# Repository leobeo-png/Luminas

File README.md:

# Luminas
Rhythm game controller development (Pro Micro). WIP <br>
[Video Demo](https://www.youtube.com/watch?v=vNHZUSEBsMY "Early Prototype")
[Video Demo](https://www.youtube.com/watch?v=JDYHQ-9xTno "Prototype Update")
---
## Description
 - Custom keyboard NKRO HID 
 - PCB size for 15.6" laptop
 - ToF sensors instead of IR for compactness
---
## Components Used:
 - Arduino Pro Micro
 - MPR121 Modules x3
 - VL53L0X ToF sensors x2 
 - TCA9548 I2C Multiplexer
 - Pull-up resistors
---
## Goals
 - Improve the design of the PCB 
 - Reaserch and design the casing
--- 
## What I Learnt so Far 
 - HID (descriptors, how NKRO works)
 - PCB schematic designing
 - Diving further into I2C

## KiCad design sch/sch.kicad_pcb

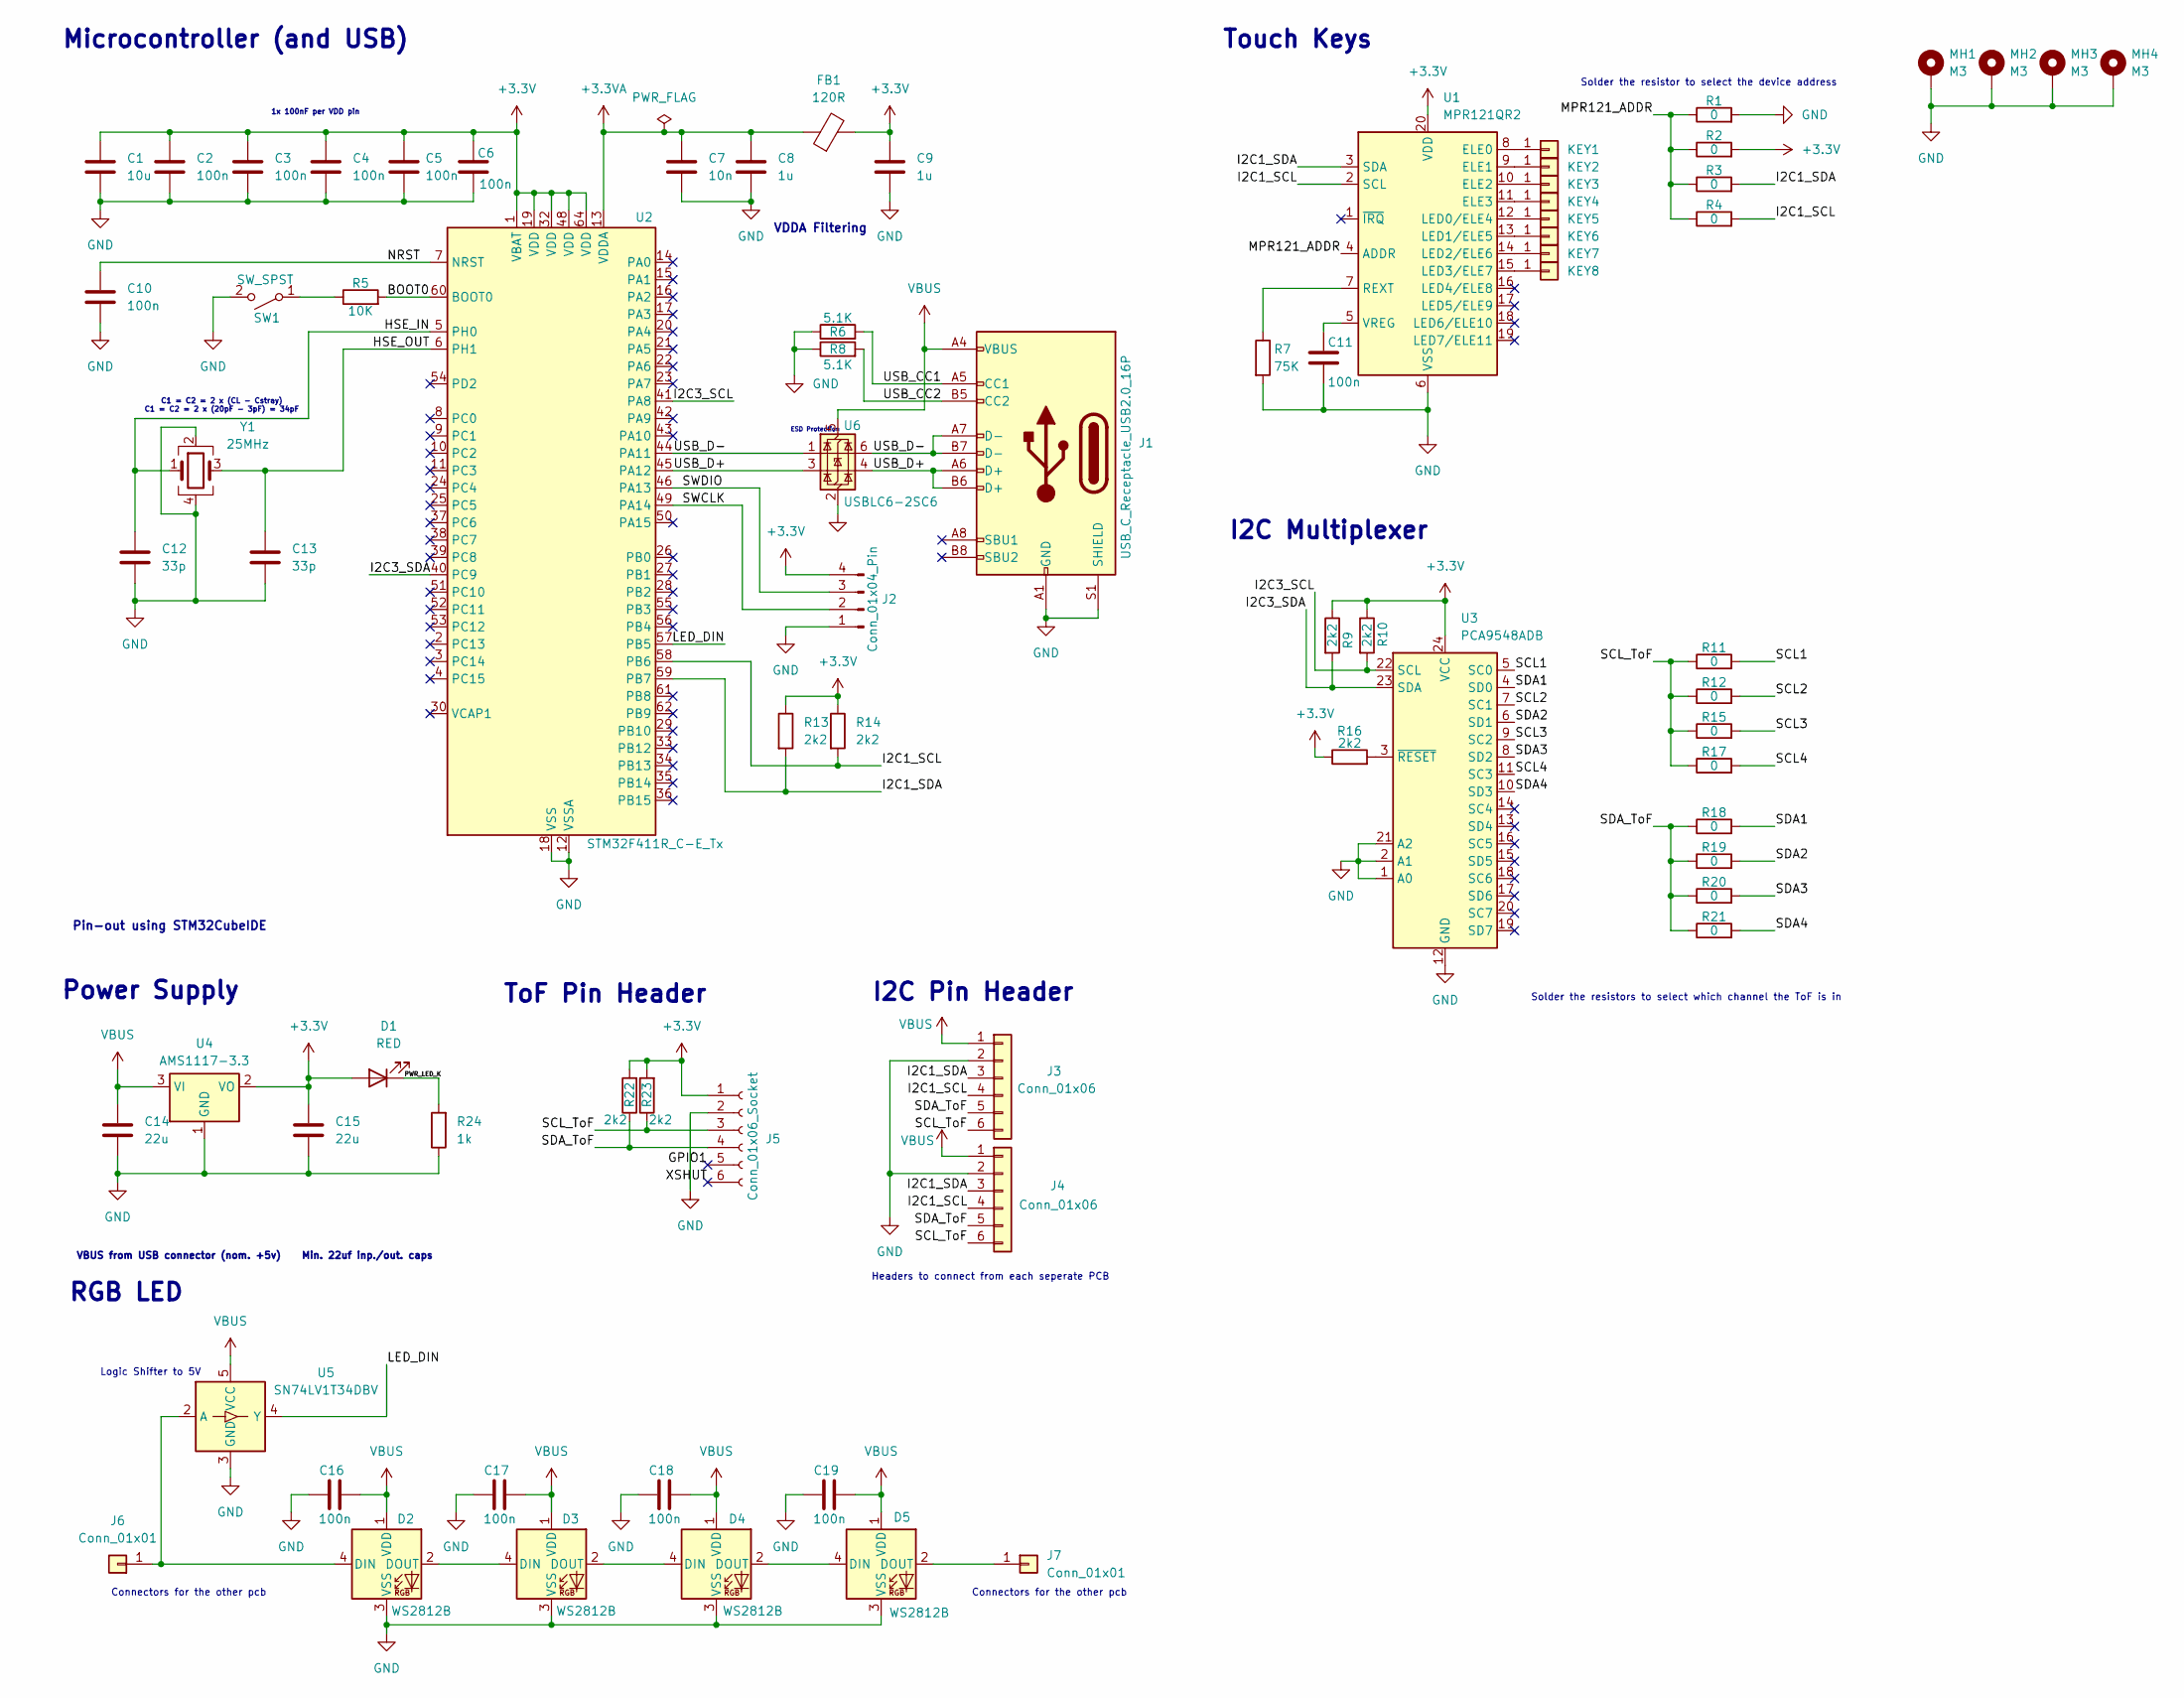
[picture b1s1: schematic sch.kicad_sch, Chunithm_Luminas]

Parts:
C1: 10u; C_0603_1608Metric_Pad1.08x0.95mm_HandSolder
C2, C3, C4, C5, C6, C10, C11, C16, C17, C18, C19: 100n; C_0603_1608Metric_Pad1.08x0.95mm_HandSolder
C7: 10n; C_0603_1608Metric_Pad1.08x0.95mm_HandSolder
C8, C9: 1u; C_0603_1608Metric_Pad1.08x0.95mm_HandSolder
C12, C13: 33p; C_0603_1608Metric_Pad1.08x0.95mm_HandSolder
C14, C15: 22u; C_0805_2012Metric
D1: RED; LED_0201_0603Metric
D2, D3, D4, D5: WS2812B; LED_WS2812B_PLCC4_5.0x5.0mm_P3.2mm
FB1: 120R; L_0603_1608Metric
J1: USB_C_Receptacle_USB2.0_16P; USB_C_Receptacle_GCT_USB4105-xx-A_16P_TopMnt_Horizontal
J2: Conn_01x04_Pin; PinHeader_1x04_P2.54mm_Vertical
J3, J4: Conn_01x06; Conn_Solder_I2C
J5: Conn_01x06_Socket; PinHeader_1x06_P2.54mm_Vertical
J6, J7: Conn_01x01; Solder_3P
KEY1, KEY2, KEY3, KEY4, KEY5, KEY6, KEY7, KEY8: Conn_01x01; ChuKey
MH1, MH2, MH3, MH4: M3; MountingHole_3.2mm_M3_Pad_Via
R1, R2, R3, R4, R11, R12, R15, R17, R18, R19, R20, R21: 0; R_0603_1608Metric_Pad0.98x0.95mm_HandSolder
R5: 10K; R_0603_1608Metric_Pad0.98x0.95mm_HandSolder
R6, R8: 5.1K; R_0603_1608Metric_Pad0.98x0.95mm_HandSolder
R7: 75K; R_0603_1608Metric_Pad0.98x0.95mm_HandSolder
R9, R10, R13, R14, R16, R22, R23: 2k2; R_0603_1608Metric_Pad0.98x0.95mm_HandSolder
R24: 1k; R_0603_1608Metric_Pad0.98x0.95mm_HandSolder
SW1: SW_SPST; SW_SPST_TS-1088-xR025
U1: MPR121QR2; UQFN-20_3x3mm_P0.4mm
U2: STM32F411R_C-E_Tx; LQFP-64_10x10mm_P0.5mm
U3: PCA9548ADB; TSSOP-24_4.4x7.8mm_P0.65mm
U4: AMS1117-3.3; SOT-223-3_TabPin2
U5: SN74LV1T34DBV; SOT-23-5
U6: USBLC6-2SC6; SOT-23-6
Y1: 25MHz; Crystal_SMD_3225-4Pin_3.2x2.5mm_HandSoldering

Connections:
+3.3V: C1.1, C2.1, C3.1, C4.1, C5.1, C6.1, C9.1, C15.1, D1.2 (A), FB1.2, J2.4, J5.1, R2.2, R9.1, R10.1, R13.1, R14.1, R16.1, R22.2, R23.2, U1.20 (VDD), U2.1 (VBAT), U2.19 (VDD), U2.32 (VDD), U2.48 (VDD), U2.64 (VDD), U3.24 (VCC), U4.2 (VO)
+3.3VA: C7.1, C8.1, FB1.1, U2.13 (VDDA)
/BOOT0: R5.2, U2.60 (BOOT0)
/GPIO1: J5.5
/HSE_IN: C12.1, U2.5 (PH0), Y1.1
/HSE_OUT: C13.1, U2.6 (PH1), Y1.3
/I2C1_SCL: J3.4, J4.4, R4.2, R14.2, U1.2 (SCL), U2.58 (PB6)
/I2C1_SDA: J3.3, J4.3, R3.2, R13.2, U1.3 (SDA), U2.59 (PB7)
/I2C3_SCL: R10.2, U2.41 (PA8), U3.22 (SCL)
/I2C3_SDA: R9.2, U2.40 (PC9), U3.23 (SDA)
/LED_DIN: U2.57 (PB5), U5.4 (Y)
/MPR121_ADDR: R1.1, R2.1, R3.1, R4.1, U1.4 (ADDR)
/NRST: C10.1, U2.7 (NRST)
/PWR_LED_K: D1.1 (K), R24.2
/SCL1: R11.2, U3.5 (SC0)
/SCL2: R12.2, U3.7 (SC1)
/SCL3: R15.2, U3.9 (SC2)
/SCL4: R17.2, U3.11 (SC3)
/SCL_ToF: J3.6, J4.6, J5.3, R11.1, R12.1, R15.1, R17.1, R23.1
/SDA1: R18.2, U3.4 (SD0)
/SDA2: R19.2, U3.6 (SD1)
/SDA3: R20.2, U3.8 (SD2)
/SDA4: R21.2, U3.10 (SD3)
/SDA_ToF: J3.5, J4.5, J5.4, R18.1, R19.1, R20.1, R21.1, R22.1
/SWCLK: J2.2, U2.49 (PA14)
/SWDIO: J2.3, U2.46 (PA13)
/USB_CC1: J1.A5 (CC1), R6.2
/USB_CC2: J1.B5 (CC2), R8.2
/USB_D+: J1.A6 (D+), J1.B6 (D+), U2.45 (PA12), U6.3 (I/O2), U6.4 (I/O2)
/USB_D-: J1.A7 (D-), J1.B7 (D-), U2.44 (PA11), U6.1 (I/O1), U6.6 (I/O1)
/XSHUT: J5.6
GND: C1.2, C2.2, C3.2, C4.2, C5.2, C6.2, C7.2, C8.2, C9.2, C10.2, C11.2, C12.2, C13.2, C14.2, C15.2, C16.1, C17.1, C18.1, C19.1, D2.3 (VSS), D3.3 (VSS), D4.3 (VSS), D5.3 (VSS), J1.A1 (GND), J1.A12 (GND), J1.B1 (GND), J1.B12 (GND), J1.S1 (SHIELD), J2.1, J3.2, J4.2, J5.2, MH1.1, MH2.1, MH3.1, MH4.1, R1.2, R6.1, R7.2, R8.1, R24.1, SW1.2 (B), U1.6 (VSS), U2.12 (VSSA), U2.18 (VSS), U2.31 (VSS), U2.47 (VSS), U2.63 (VSS), U3.1 (A0), U3.2 (A1), U3.12 (GND), U3.21 (A2), U4.1 (GND), U5.3 (GND), U6.2 (GND), Y1.2, Y1.4
unnamed: D2.4 (DIN), J6.1, U5.2 (A)
unnamed: D2.2 (DOUT), D3.4 (DIN)
unnamed: D3.2 (DOUT), D4.4 (DIN)
unnamed: D4.2 (DOUT), D5.4 (DIN)
unnamed: D5.2 (DOUT), J7.1
unnamed: KEY1.1, U1.8 (ELE0)
unnamed: KEY2.1, U1.9 (ELE1)
unnamed: KEY3.1, U1.10 (ELE2)
unnamed: KEY4.1, U1.11 (ELE3)
unnamed: KEY5.1, U1.12 (LED0/ELE4)
unnamed: KEY6.1, U1.13 (LED1/ELE5)
unnamed: KEY7.1, U1.14 (LED2/ELE6)
unnamed: KEY8.1, U1.15 (LED3/ELE7)
unnamed: R5.1, SW1.1 (A)
unnamed: R7.1, U1.7 (REXT)
unnamed: C11.1, U1.5 (VREG)
unnamed: R16.2, U3.3 (~RESET)
VBUS: C14.1, C16.2, C17.2, C18.2, C19.2, D2.1 (VDD), D3.1 (VDD), D4.1 (VDD), D5.1 (VDD), J1.A4 (VBUS), J1.A9 (VBUS), J1.B4 (VBUS), J1.B9 (VBUS), J3.1, J4.1, U4.3 (VI), U5.5 (VCC), U6.5 (VBUS)

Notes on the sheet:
Connectors for the other pcb
I2C Multiplexer
Solder the resistors to select which channel the ToF is in
VBUS from USB connector (nom. +5v) Min. 22uf inp./out. caps
Headers to connect from each seperate PCB
Microcontroller (and USB)
ESD Protection
VDDA Filtering
RGB LED
1x 100nF per VDD pin
I2C Pin Header
Solder the resistor to select the device address
Power Supply
Logic Shifter to 5V
Pin-out using STM32CubeIDE
Touch Keys
ToF Pin Header
C1 = C2 = 2 x (CL - Cstray) C1 = C2 = 2 x (20pF - 3pF) = 34pF

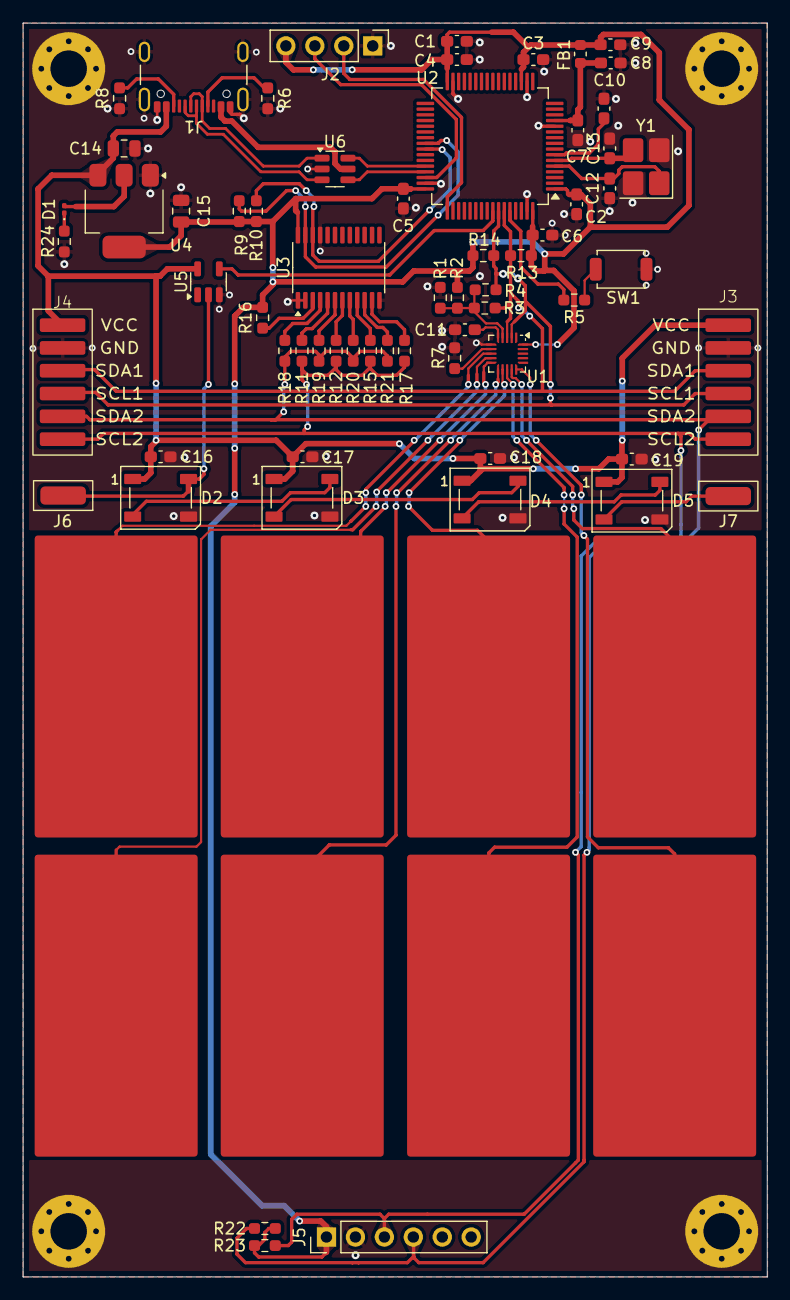
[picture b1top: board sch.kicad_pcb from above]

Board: 2 copper layers, 65.3 x 110.0 mm, 76 parts (0 on the bottom side), 48 nets.

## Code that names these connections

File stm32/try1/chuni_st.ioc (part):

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Mcu.Name=STM32F411C(C-E)Ux
Mcu.Package=UFQFPN48
Mcu.UserName=STM32F411CEUx
PA11.Mode=Device_Only
PA11.Signal=USB_OTG_FS_DM
PA12.Mode=Device_Only
PA12.Signal=USB_OTG_FS_DP
PA13.Mode=Serial_Wire
PA13.Signal=SYS_JTMS-SWDIO
PA14.Mode=Serial_Wire
PA14.Signal=SYS_JTCK-SWCLK
PB10.Mode=I2C
PB10.Signal=I2C2_SCL
PB3.Mode=I2C
PB3.Signal=I2C2_SDA
PB6.Mode=I2C
PB6.Signal=I2C1_SCL
PB7.Mode=I2C
PB7.Signal=I2C1_SDA
PC13-ANTI_TAMP.Signal=GPIO_Output
PH0\ -\ OSC_IN.Mode=HSE-External-Oscillator
PH0\ -\ OSC_IN.Signal=RCC_OSC_IN
PH1\ -\ OSC_OUT.Mode=HSE-External-Oscillator
PH1\ -\ OSC_OUT.Signal=RCC_OSC_OUT
RCC.HSE_VALUE=25000000
RCC.SYSCLKFreq_VALUE=96000000
RCC.SYSCLKSource=RCC_SYSCLKSOURCE_PLLCLK
board=custom

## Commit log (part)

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2024-11-06 First Itteration
    This version includes working NKRO and ToF. Although it might
    occasionally crash, probably because of memory? But i still don't know.
2024-11-06 Update README.md
    Updated it to its current state
2024-11-11 Fixed air keys
2025-04-01 Added Schematics and updated title
2025-04-01 Updated video
2025-05-05 Updated PCB
2025-05-05 ATMEGA32U4 option
2025-05-07 Working code for the prototype board
2025-05-07 Updated schematic for Pro Micro
2025-10-13 improvements for first prototype
    added 3 mpr121 support, haven't figured out crashing issue
2025-10-15 STM32F411CEU6 Implementation
    ported the code into stm32 platform for more robustness on the i2c bus.
2026-02-11 fixed missing pull up on multiplexer
2026-02-11 first revision
2026-03-02 Cleaned the branch with only relevant files
    It was a mess, trying to clean it up and manage the git properly
2026-03-02 Revision 2 of the PCB
    Updated to using stm32f4 and a more modular design
2026-03-27 Updated side pads with power and ground
2026-06-11 gpy2 sensor instead of tof
